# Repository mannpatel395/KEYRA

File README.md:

# KEYRA
A compact 2×2 KMK-based macro pad built on the XIAO RP2040, featuring a diode-protected key matrix, rotary encoder, and OLED display. Designed as a clean, USB-powered control device for macros, navigation, and everyday hardware tinkering.

## Preview:

-------------------------------------------------------------------------------------------------------------------------------------------------------------------------------------------------------------------------------------------------------------------------------

## Features:

Dual layer acrylic case.

128x32 OLED Display

EC11 Rotary encoder

4 Keys

-------------------------------------------------------------------------------------------------------------------------------------------------------------------------------------------------------------------------------------------------------------------------------

## CAD:

Everthing combines with 4 M3 bolts and it has 2 printable parts.

Hell Fushion360!!

-------------------------------------------------------------------------------------------------------------------------------------------------------------------------------------------------------------------------------------------------------------------------------

## PCB:

Simple PCB made in KiCad!

Schematic

Footprints

PCB

-------------------------------------------------------------------------------------------------------------------------------------------------------------------------------------------------------------------------------------------------------------------------------

## Firmware:
The device runs KMK firmware, which turns the RP2040 into a fully programmable USB keyboard.
It scans a diode-protected key matrix, handles the rotary encoder, and communicates with the OLED over I²C.

I do have many ideas but stoping now till here.

-------------------------------------------------------------------------------------------------------------------------------------------------------------------------------------------------------------------------------------------------------------------------------

## BOM:

4x Cherry MX Switches

4x DSA Keycaps

4X M3x12mm SHCS Bolts

4x 1N4148WT DO-35 Diodes

1x 0.91" 128x32 OLED Display

1x EC11 Rotary Encoder

1x XIAO RP2040

1x Case (2 printed parts)

-------------------------------------------------------------------------------------------------------------------------------------------------------------------------------------------------------------------------------------------------------------------------------

Thats all for now will update this whenever ideas sparks and time permites.

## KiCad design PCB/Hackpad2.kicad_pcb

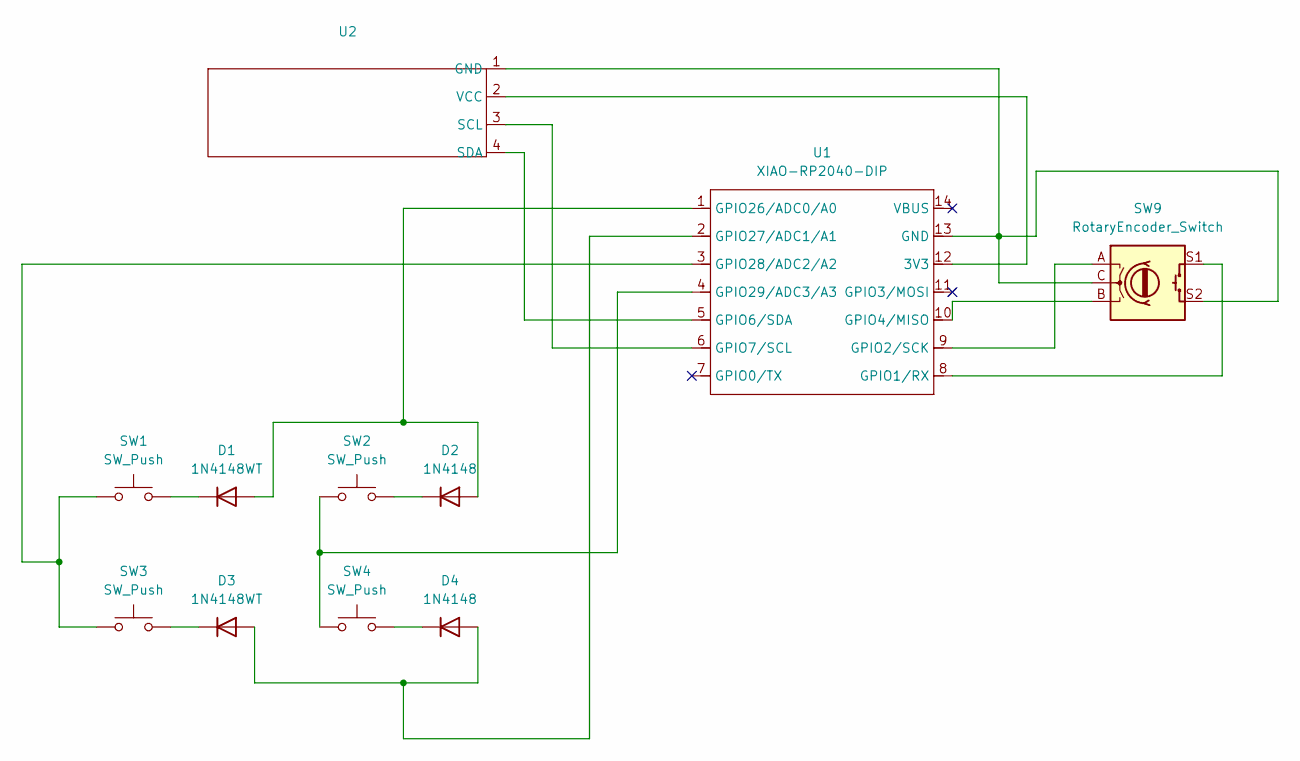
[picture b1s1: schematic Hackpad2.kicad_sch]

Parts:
D1, D3: 1N4148WT; D_DO-35_SOD27_P7.62mm_Horizontal
D2, D4: 1N4148; D_DO-35_SOD27_P7.62mm_Horizontal
SW1, SW2, SW3, SW4: SW_Push; SW_Cherry_MX_1.00u_PCB
SW9: RotaryEncoder_Switch; RotaryEncoder_Alps_EC11E-Switch_Vertical_H20mm
U1: XIAO-RP2040-DIP
U2: SSD1306-0.91-OLED-4pin-128x32

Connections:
unnamed: D1.2 (A), D2.2 (A), U1.1 (GPIO26/ADC0/A0)
unnamed: D1.1 (K), SW1.2
unnamed: D2.1 (K), SW2.2
unnamed: D3.2 (A), D4.2 (A), U1.2 (GPIO27/ADC1/A1)
unnamed: D3.1 (K), SW3.2
unnamed: D4.1 (K), SW4.2
unnamed: U1.12 (3V3), U2.2 (VCC)
unnamed: SW9.C, SW9.S2, U1.13 (GND), U2.1 (GND)
unnamed: SW9.S1, U1.8 (GPIO1/RX)
unnamed: SW9.A, U1.9 (GPIO2/SCK)
unnamed: SW9.B, U1.10 (GPIO4/MISO)
unnamed: U1.5 (GPIO6/SDA), U2.4 (SDA)
unnamed: U1.6 (GPIO7/SCL), U2.3 (SCL)
unnamed: SW1.1, SW3.1, U1.3 (GPIO28/ADC2/A2)
unnamed: SW2.1, SW4.1, U1.4 (GPIO29/ADC3/A3)

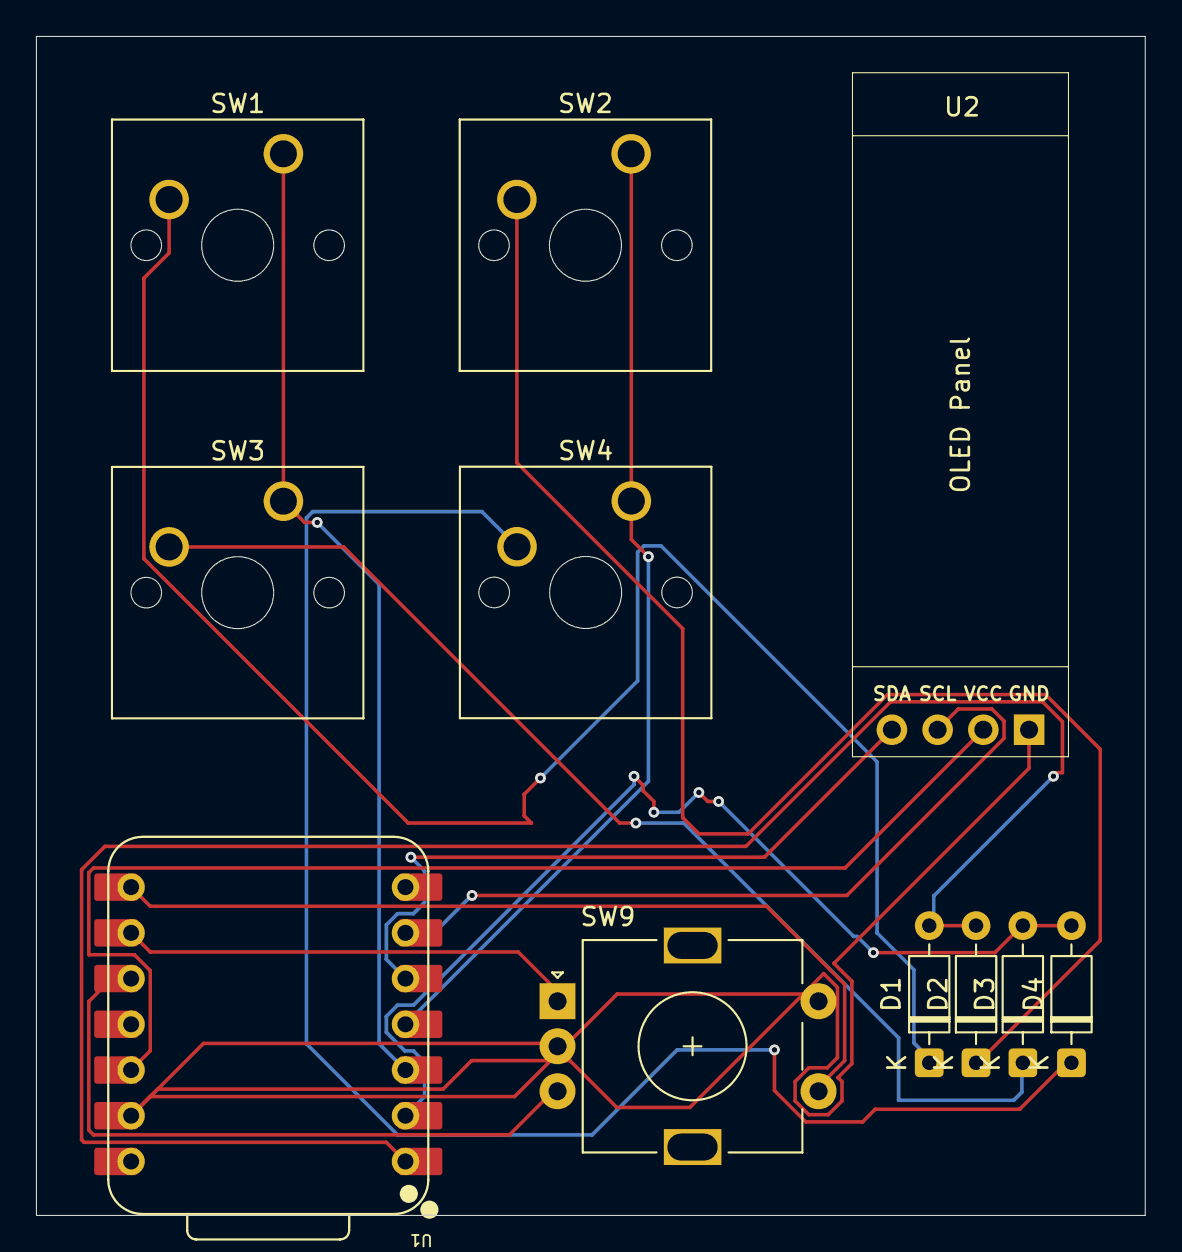
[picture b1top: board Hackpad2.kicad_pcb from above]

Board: 2 copper layers, 61.6 x 65.5 mm, 11 parts (0 on the bottom side), 15 nets.

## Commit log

2026-02-07 Create mas
2026-02-07 Create m
2026-02-07 Create a
2026-02-07 Create as
2026-02-10 Create asasd
